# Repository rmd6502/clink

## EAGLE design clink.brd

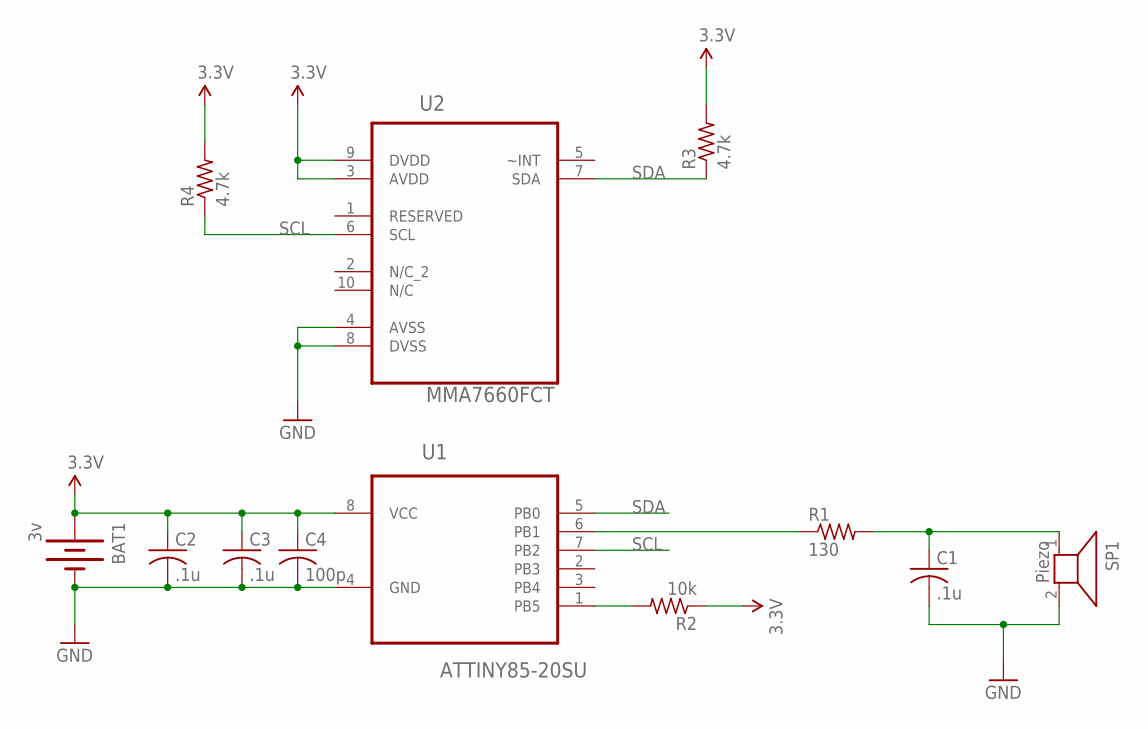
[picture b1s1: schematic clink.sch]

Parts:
BAT1: 3v; BATTCON_20MM
C1, C2, C3: .1u; C0603
C4: 100p; C0603
R1: 130; R0603
R2: 10k; R0603
R3, R4: 4.7k; R0603
SP1: Piezo; AL201P
U1: ATTINY85-20SU; SOIC127P798X216-8N
U2: MMA7660FCT; DFN300X300X100-10N

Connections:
3.3V: BAT1.1 (+), C2.1, C3.1, C4.1, R2.1, R3.2, R4.2, U1.8 (VCC), U2.3 (AVDD), U2.9 (DVDD)
GND: BAT1.2 (-), C1.2, C2.2, C3.2, C4.2, SP1.2, U1.4 (GND), U2.4 (AVSS), U2.8 (DVSS)
unnamed: C1.1, R1.2, SP1.1
unnamed: R1.1, U1.6 (PB1)
unnamed: R2.2, U1.1 (PB5)
SCL: R4.1, U1.7 (PB2), U2.6 (SCL)
SDA: R3.1, U1.5 (PB0), U2.7 (SDA)

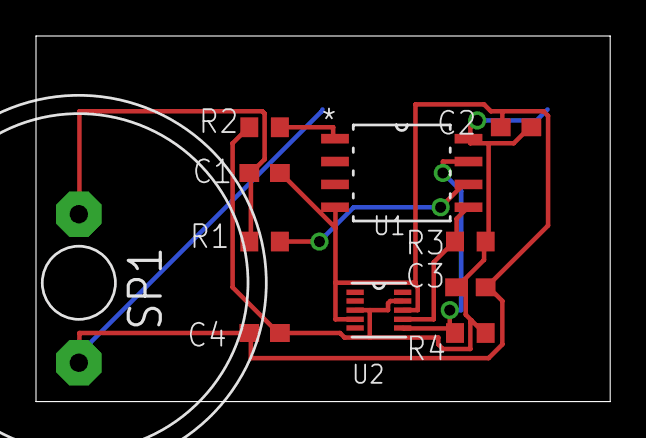
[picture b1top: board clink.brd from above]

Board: 2 copper layers, 31.9 x 20.3 mm, 12 parts (1 on the bottom side), 7 nets.

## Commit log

2014-02-06 initial
2014-02-06 move files

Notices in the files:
parts and their libraries:
SparkFun-Electromechanical: Licensing: CC v3.0 Share-Alike You are welcome to use this library for commercial purposes.
